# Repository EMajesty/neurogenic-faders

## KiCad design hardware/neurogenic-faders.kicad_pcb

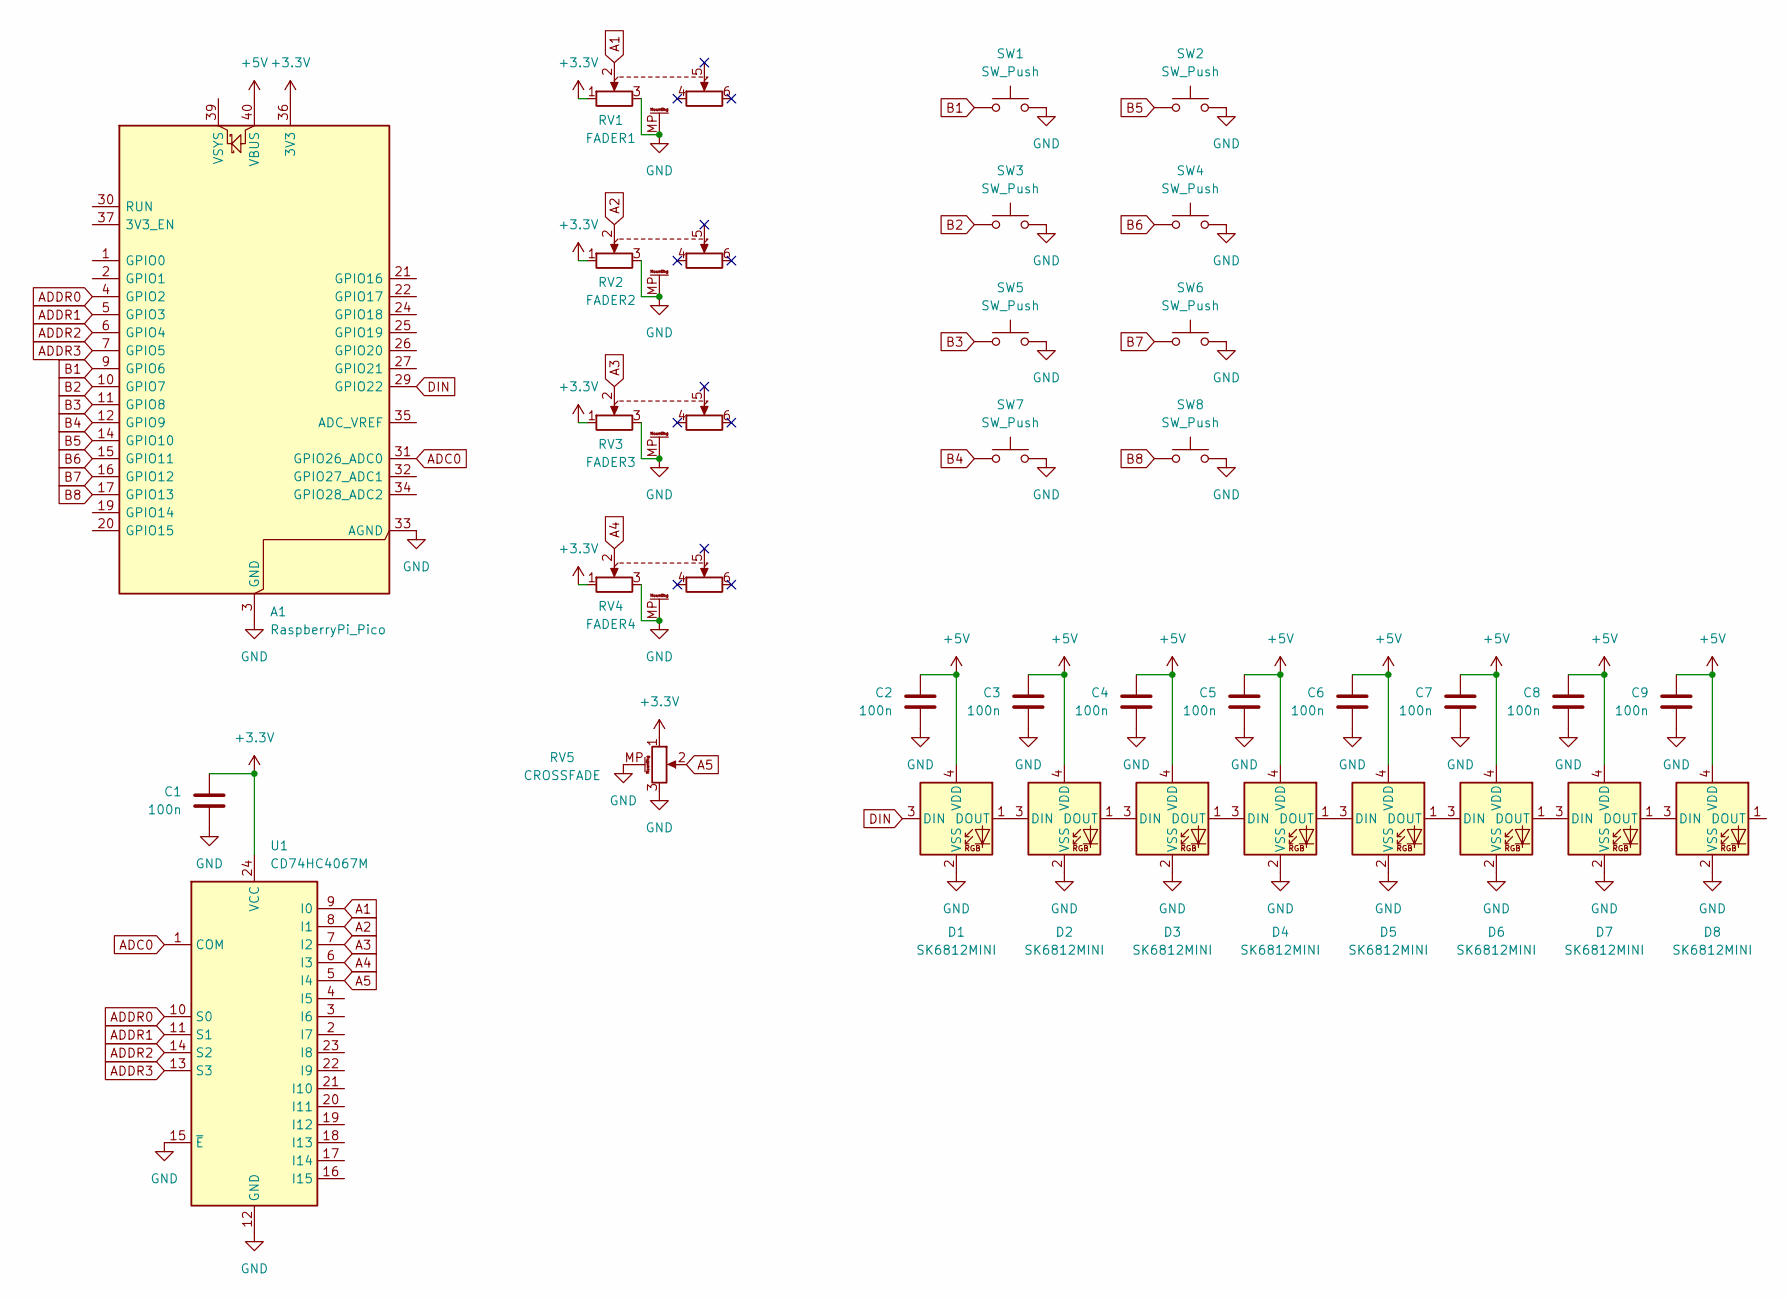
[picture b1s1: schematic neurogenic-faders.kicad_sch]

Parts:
A1: RaspberryPi_Pico; RaspberryPi_Pico_Common_Unspecified
C1, C2, C3, C4, C5, C6, C7, C8, C9: 100n; C_0805_2012Metric_Pad1.18x1.45mm_HandSolder
D1, D2, D3, D4, D5, D6, D7, D8: SK6812MINI; SK6812MINIE
RV1: FADER1; Fader Stereo 60mm
RV2: FADER2; Fader Stereo 60mm
RV3: FADER3; Fader Stereo 60mm
RV4: FADER4; Fader Stereo 60mm
RV5: CROSSFADE; Fader Mono 30mm
SW1, SW2, SW3, SW4, SW5, SW6, SW7, SW8: SW_Push; SW_PG1350
U1: CD74HC4067M; SOIC-24W_7.5x15.4mm_P1.27mm

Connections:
+3.3V: A1.36 (3V3), C1.1, RV1.1, RV2.1, RV3.1, RV4.1, RV5.1, U1.24 (VCC)
+5V: A1.40 (VBUS), C2.1, C3.1, C4.1, C5.1, C6.1, C7.1, C8.1, C9.1, D1.4 (VDD), D2.4 (VDD), D3.4 (VDD), D4.4 (VDD), D5.4 (VDD), D6.4 (VDD), D7.4 (VDD), D8.4 (VDD)
A1: RV1.2, U1.9 (I0)
A2: RV2.2, U1.8 (I1)
A3: RV3.2, U1.7 (I2)
A4: RV4.2, U1.6 (I3)
A5: RV5.2, U1.5 (I4)
ADC0: A1.31 (GPIO26_ADC0), U1.1 (COM)
ADDR0: A1.4 (GPIO2), U1.10 (S0)
ADDR1: A1.5 (GPIO3), U1.11 (S1)
ADDR2: A1.6 (GPIO4), U1.14 (S2)
ADDR3: A1.7 (GPIO5), U1.13 (S3)
B1: A1.9 (GPIO6), SW1.1
B2: A1.10 (GPIO7), SW3.1
B3: A1.11 (GPIO8), SW5.1
B4: A1.12 (GPIO9), SW7.1
B5: A1.14 (GPIO10), SW2.1
B6: A1.15 (GPIO11), SW4.1
B7: A1.16 (GPIO12), SW6.1
B8: A1.17 (GPIO13), SW8.1
DIN: A1.29 (GPIO22), D1.3 (DIN)
GND: A1.3 (GND), A1.8 (GND), A1.13 (GND), A1.18 (GND), A1.23 (GND), A1.28 (GND), A1.33 (AGND), A1.38 (GND), C1.2, C2.2, C3.2, C4.2, C5.2, C6.2, C7.2, C8.2, C9.2, D1.2 (VSS), D2.2 (VSS), D3.2 (VSS), D4.2 (VSS), D5.2 (VSS), D6.2 (VSS), D7.2 (VSS), D8.2 (VSS), RV1.3, RV1.MP (MountPin), RV2.3, RV2.MP (MountPin), RV3.3, RV3.MP (MountPin), RV4.3, RV4.MP (MountPin), RV5.3, RV5.MP (MountPin), SW1.2, SW2.2, SW3.2, SW4.2, SW5.2, SW6.2, SW7.2, SW8.2, U1.12 (GND), U1.15 (~E)
unnamed: D1.1 (DOUT), D2.3 (DIN)
unnamed: D2.1 (DOUT), D3.3 (DIN)
unnamed: D3.1 (DOUT), D4.3 (DIN)
unnamed: D4.1 (DOUT), D5.3 (DIN)
unnamed: D5.1 (DOUT), D6.3 (DIN)
unnamed: D6.1 (DOUT), D7.3 (DIN)
unnamed: D7.1 (DOUT), D8.3 (DIN)

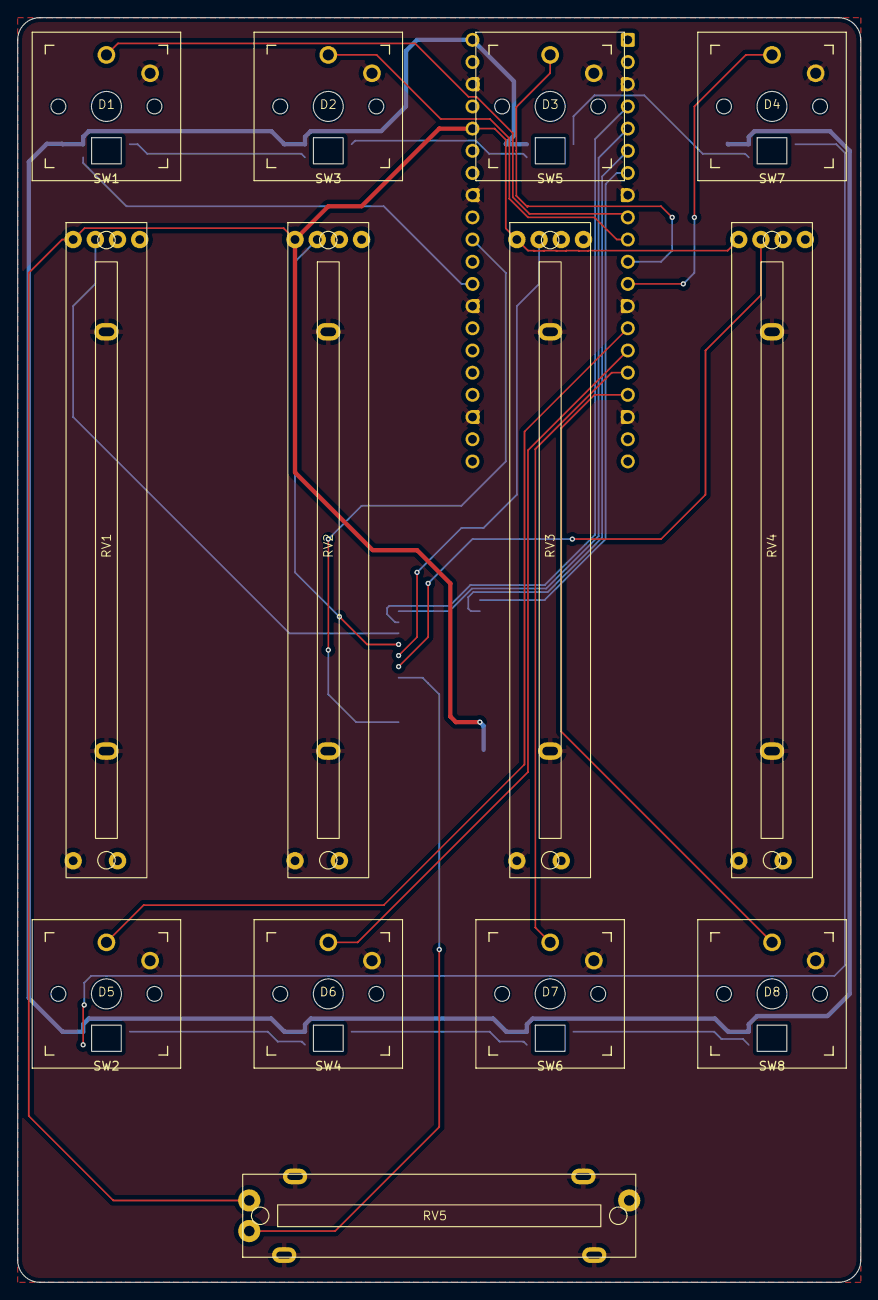
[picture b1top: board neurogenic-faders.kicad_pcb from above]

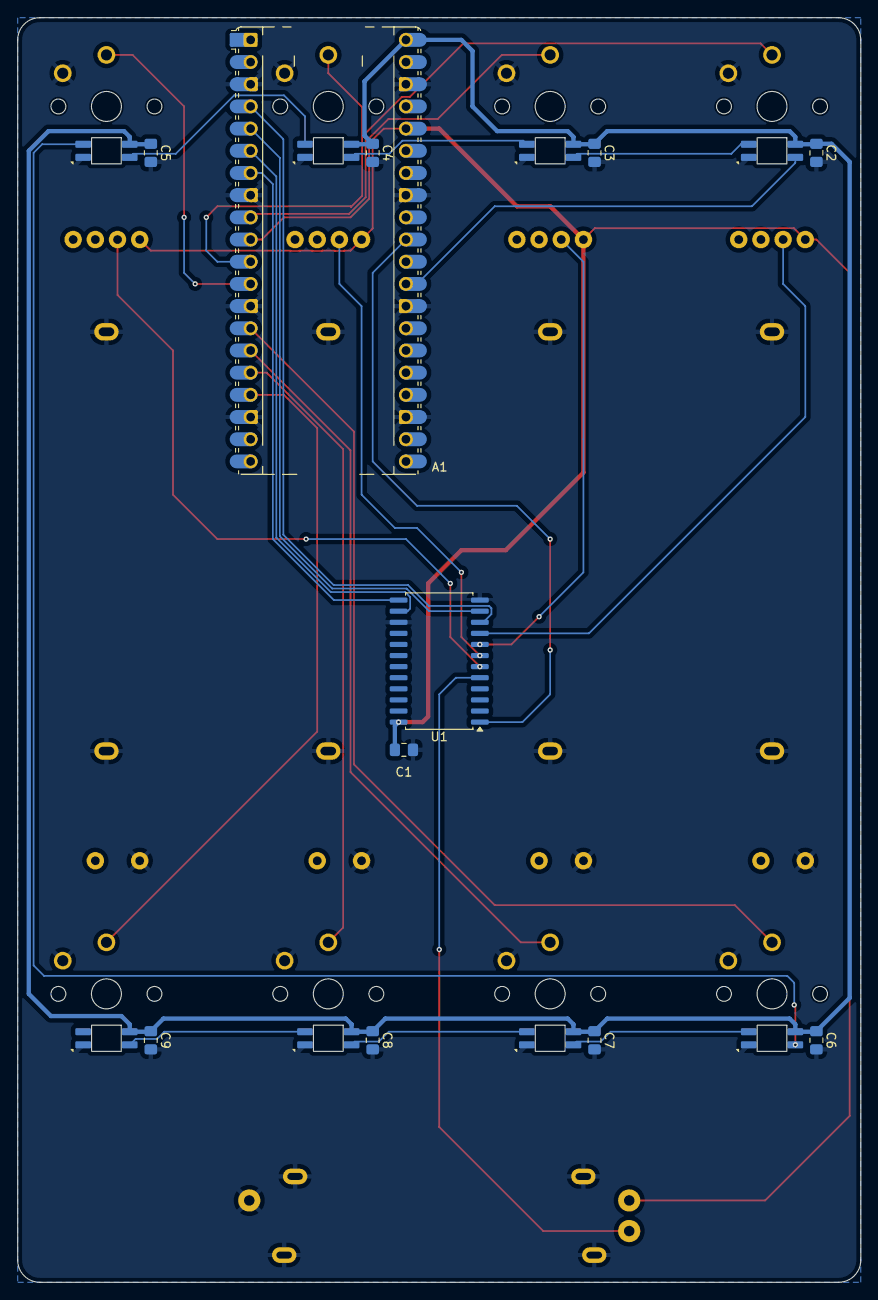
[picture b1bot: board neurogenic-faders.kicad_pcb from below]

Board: 2 copper layers, 96.5 x 144.8 mm, 32 parts (11 on the bottom side), 29 nets.
